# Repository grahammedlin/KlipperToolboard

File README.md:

# Huvud 3D Printer toolhead board USB-PD

A very small 3D printer board for use on a direct drive toolhead. 
It is designed to be used with Klipper firmware.
Klipper has the awesome feature to be able to use multiple MCUs connected to the host over a (relatively) high latency connection. 
This version uses USB-PD instead of CAN. 
Why? USB-C adoption makes premade, robust, and flexible cables capable of supplying power and data generally availabile as commodities.
Also, for fun.
It runs at 20 V instead of 24 V, so maximum fan speed is a little slower. 
24 V is technically possible with USB-PD 3.1 EPR AVS, but the hardware is not commonplace. 

---

Based on the amazing work of [bondus](https://github.com/bondus/KlipperToolboard)

Buy it at:

* Lukes Lab: https://lukeslabonline.com/products/huvud
* Tindie: https://www.tindie.com/products/huvud/huvud-3d-printer-hotend-control-board/

Read more about the project activites over at hackaday:
https://hackaday.io/project/174429-huvud-a-3d-printer-tool-head-controller-board

---

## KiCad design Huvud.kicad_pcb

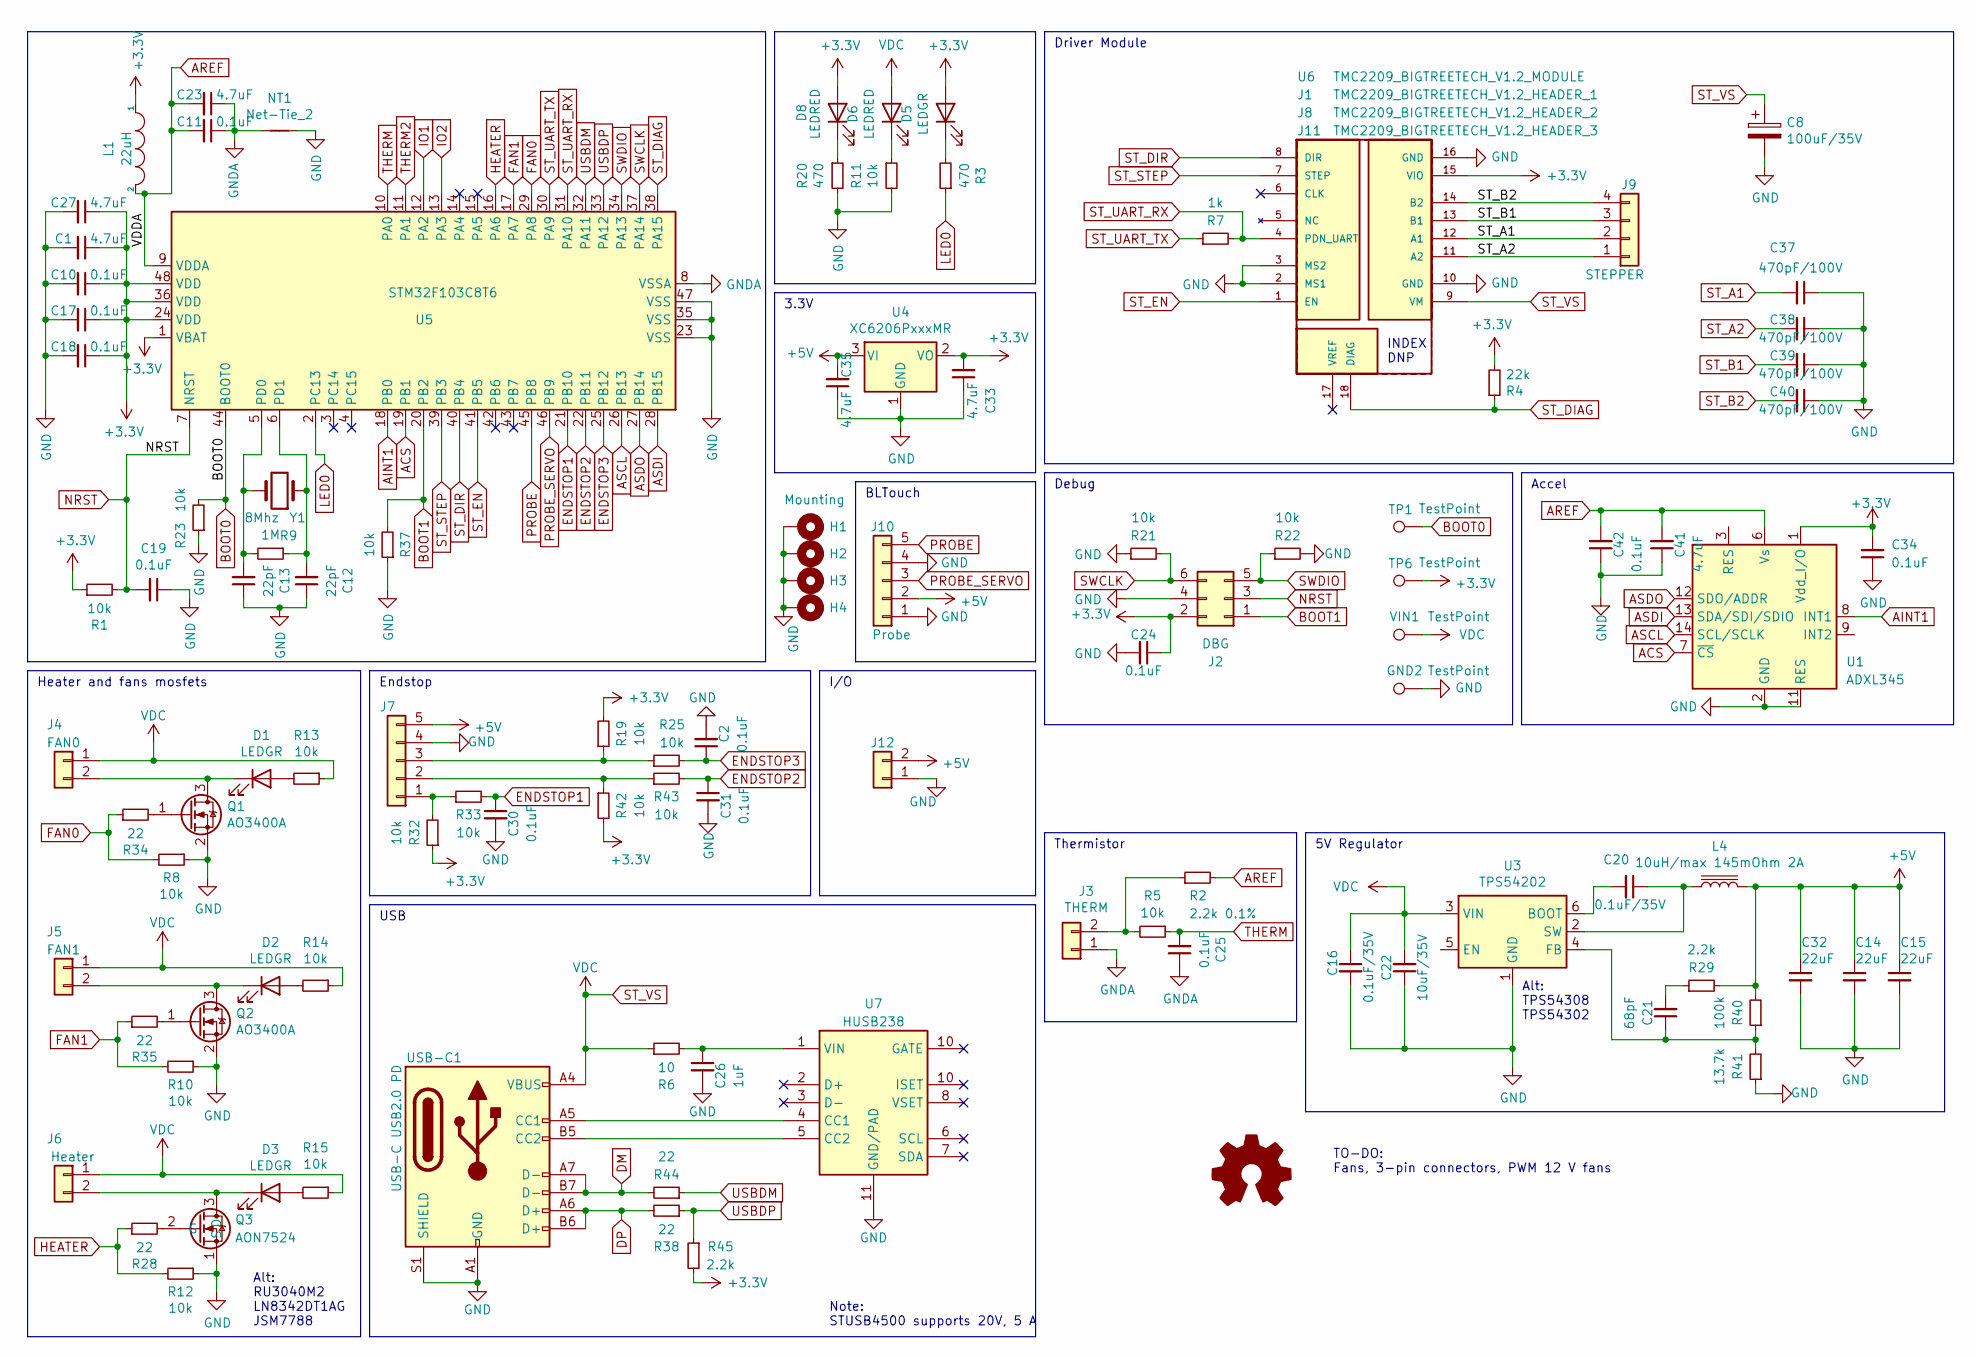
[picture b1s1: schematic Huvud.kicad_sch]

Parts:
C1, C23, C27, C33, C35, C41: 4.7uF; C_0402_1005Metric; LCSC C23733
C2, C11, C17, C18, C19, C24, C25, C30, C31: 0.1uF; C_0402_1005Metric
C8: 100uF/35V; CP_Elec_6.3x5.8; LCSC C249982
C10, C34, C42: 0.1uF; C_0402_1005Metric; LCSC C1525
C12: 22pF; C_0402_1005Metric; LCSC C1555
C13: 22pF; C_0402_1005Metric
C14, C15, C32: 22uF; C_0805_2012Metric; LCSC C45783
C16, C20: 0.1uF/35V; C_0603_1608Metric; LCSC C14663
C21: 68pF; C_0402_1005Metric; LCSC C14441
C22: 10uF/35V; C_1210_3225Metric; LCSC C13585
C26: 1uF; C_0402_1005Metric
C37, C38, C39, C40: 470pF/100V; C_0603_1608Metric; LCSC C107062
D1, D2, D3, D5: LEDGR; LED_0402_1005Metric; LCSC C74338
D6, D8: LEDRED; LED_0603_1608Metric; LCSC C2286
GND2: TestPoint; TestPoint_Pad_D1.0mm
H1: Mounting; MountingHole_3.2mm_M3_Pad_Via
H2, H3, H4: MountingHole; MountingHole_3.2mm_M3_Pad_Via
J1: TMC2209_BIGTREETECH_V1.2_HEADER_1; HEADER_TMC2209_BIGTREETECH_1
J2: DBG; PinHeader_2x03_P2.54mm_Vertical; LCSC C65114
J3: THERM; JST_PH_B2B-PH-K_1x02_P2.00mm_Vertical; LCSC C2320
J4: FAN0; JST_PH_B2B-PH-K_1x02_P2.00mm_Vertical; LCSC C2319
J5: FAN1; JST_PH_B2B-PH-K_1x02_P2.00mm_Vertical; LCSC C2319
J6: Heater; TerminalBlock_TE_282834-2_1x02_P2.54mm_Horizontal; LCSC C557685
J7: Endstop; JST_PH_B5B-PH-K_1x05_P2.00mm_Vertical; LCSC C2322
J8: TMC2209_BIGTREETECH_V1.2_HEADER_2; HEADER_TMC2209_BIGTREETECH_2
J9: STEPPER; JST_PH_B4B-PH-K_1x04_P2.00mm_Vertical; LCSC C144395
J10: Probe; PinHeader_1x05_P2.54mm_Vertical; LCSC C2322
J11: TMC2209_BIGTREETECH_V1.2_HEADER_3; HEADER_TMC2209_BIGTREETECH_3
J12: 5V; PinHeader_1x02_P2.54mm_Vertical; LCSC C2322
L1: 22uH; L_0805_2012Metric; LCSC C32375
L4: 10uH/max 145mOhm 2A; L_Sunlord_MWSA0518_5.4x5.2mm; LCSC C408412
LOGO1: Logo_Open_Hardware_Small; OSHW-Symbol_6.7x6mm_SilkScreen
NT1: Net-Tie_2; NetTie-2_SMD_Pad0.5mm
Q1, Q2: AO3400A; SOT-23; LCSC C20917
Q3: AON7524; DFN-8-1EP_3x3mm_P0.65mm_EP1.7x2.05mm; LCSC C431195
R1, R5, R8, R10, R12, R13, R14, R15, R21, R23: 10k; R_0402_1005Metric; LCSC C25744
R2: 2.2k 0.1%; R_0402_1005Metric; LCSC C445604
R3, R20: 470; R_0402_1005Metric; LCSC C25117
R4: 22k; R_0402_1005Metric; LCSC C25768
R6: 10; R_0402_1005Metric; LCSC C25744
R7: 1k; R_0402_1005Metric; LCSC C21190
R9: 1M; R_0402_1005Metric; LCSC C26083
R11, R19, R22, R25, R32, R33, R37, R42, R43: 10k; R_0402_1005Metric
R28, R35, R44: 22; R_0402_1005Metric
R29, R45: 2.2k; R_0402_1005Metric; LCSC C25879
R34, R38: 22; R_0402_1005Metric; LCSC C25092
R40: 100k; R_0402_1005Metric; LCSC C25741
R41: 13.7k; R_0402_1005Metric; LCSC C25854
TP1, TP6: TestPoint; TestPoint_Pad_D1.0mm
U1: ADXL345; LGA-14_3x5mm_P0.8mm_LayoutBorder1x6y; LCSC C9667
U3: TPS54202; SOT-23-6; LCSC C191884
U4: XC6206PxxxMR; SOT-23; LCSC C5446
U5: STM32F103C8T6; LQFP-48_7x7mm_P0.5mm; LCSC C8734
U6: TMC2209_BIGTREETECH_V1.2_MODULE; MODULE_TMC2209_BIGTREETECH; PARTREV 1.20
U7: HUSB238; DFN-10-1EP_3x3mm_P0.5mm_EP1.7x2.5mm
USB-C1: USB-C USB2.0 PD; USB_C_Receptacle_GT-USB-7010
VIN1: TestPoint; TestPoint_Pad_D1.0mm
Y1: 8Mhz; Crystal_SMD_5032-2Pin_5.0x3.2mm; LCSC C115962

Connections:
+3V3: C1.1, C10.1, C17.1, C18.1, C24.1, C27.1, C33.2, C34.2, D5.2 (A), D8.2 (A), J2.2, J8.15 (VIO), L1.1, R1.1, R4.2, R19.2, R32.1, R42.2, R45.2, TP6.1, U1.1 (Vdd_I/O), U4.2 (VO), U5.1 (VBAT), U5.24 (VDD), U5.36 (VDD), U5.48 (VDD)
+5V: C14.1, C15.1, C32.1, C35.2, J7.5, J10.2, J12.2, L4.2, R29.2, R40.2, U4.3 (VI)
ACS: U1.7 (~CS), U5.19 (PB1)
AINT1: U1.8 (INT1), U5.18 (PB0)
AREF: C11.2, C23.2, C41.2, C42.2, L1.2, R2.2, U1.6 (Vs), U5.9 (VDDA)
ASCL: U1.14 (SCL/SCLK), U5.26 (PB13)
ASDI: U1.13 (SDA/SDI/SDIO), U5.28 (PB15)
ASDO: U1.12 (SDO/ADDR), U5.27 (PB14)
BOOT0: R23.2, TP1.1, U5.44 (BOOT0)
BOOT1: J2.1, R37.2, U5.20 (PB2)
DM: R44.2, USB-C1.A7 (D-), USB-C1.B7 (D-)
DP: R38.2, USB-C1.A6 (D+), USB-C1.B6 (D+)
ENDSTOP1: C30.1, R33.2, U5.21 (PB10)
ENDSTOP2: C31.1, R43.2, U5.22 (PB11)
ENDSTOP3: C2.1, R25.2, U5.25 (PB12)
FAN0: R8.2, R34.1, U5.29 (PA8)
FAN1: R10.2, R35.1, U5.17 (PA7)
GND: C1.2, C2.2, C8.2, C10.2, C12.1, C13.1, C14.2, C15.2, C16.2, C17.2, C18.2, C19.1, C22.1, C24.2, C26.2, C27.2, C30.2, C31.2, C32.2, C33.1, C34.1, C35.1, C37.1, C38.1, C39.1, C40.1, C41.1, C42.1, GND2.1, H1.1, H2.1, H3.1, H4.1, J1.2 (MS1), J1.3 (MS2), J2.4, J7.4, J8.10 (GND), J8.16 (GND), J10.1, J10.4, J12.1, NT1.1, Q1.2 (S), Q2.2 (S), Q3.1 (S), R8.1, R10.1, R11.2, R12.1, R20.2, R21.1, R22.2, R23.1, R37.1, R41.1, U1.2 (GND), U1.4 (GND), U1.5 (GND), U1.11 (RES), U3.1 (GND), U4.1 (GND), U5.23 (VSS), U5.35 (VSS), U5.47 (VSS), U7.11 (GND/PAD), USB-C1.A1 (GND), USB-C1.A12 (GND), USB-C1.B1 (GND), USB-C1.B12 (GND), USB-C1.S1 (SHIELD)
GNDA: C11.1, C23.1, C25.1, J3.1, NT1.2, U5.8 (VSSA)
HEATER: R12.2, R28.1, U5.16 (PA6)
IO1: U5.12 (PA2)
IO2: U5.13 (PA3)
LED0: R3.1, U5.2 (PC13)
NRST: C19.2, J2.3, R1.2, U5.7 (NRST)
unnamed: C21.2, R29.1
unnamed: D1.2 (A), R13.2
unnamed: D1.1 (K), J4.2, Q1.3 (D)
unnamed: D2.2 (A), R14.2
unnamed: D2.1 (K), J5.2, Q2.3 (D)
unnamed: D3.2 (A), R15.2
unnamed: D3.1 (K), J6.2, Q3.3 (D)
unnamed: D5.1 (K), R3.2
unnamed: D6.1 (K), R11.1
unnamed: D8.1 (K), R20.1
unnamed: J3.2, R2.1, R5.2
unnamed: J7.1, R32.2, R33.1
unnamed: J7.2, R42.1, R43.1
unnamed: J7.3, R19.1, R25.1
unnamed: Q1.1 (G), R34.2
unnamed: Q2.1 (G), R35.2
unnamed: Q3.2 (G), R28.2
unnamed: C20.2, U3.6 (BOOT)
unnamed: C21.1, R40.1, R41.2, U3.4 (FB)
unnamed: C20.1, L4.1, U3.2 (SW)
unnamed: C13.2, R9.2, U5.5 (PD0), Y1.2
unnamed: C12.2, R9.1, U5.6 (PD1), Y1.1
unnamed: U7.4 (CC1), USB-C1.A5 (CC1)
unnamed: U7.5 (CC2), USB-C1.B5 (CC2)
unnamed: C26.1, R6.2, U7.1 (VIN)
PROBE: J10.5, U5.45 (PB8)
PROBE_SERVO: J10.3, U5.46 (PB9)
ST_A1: C37.2, J8.12 (A1), J9.2
ST_A2: C38.2, J8.11 (A2), J9.1
ST_B1: C39.2, J8.13 (B1), J9.3
ST_B2: C40.2, J8.14 (B2), J9.4
ST_DIAG: J11.18 (DIAG), R4.1, U5.38 (PA15)
ST_DIR: J1.8 (DIR), U5.40 (PB4)
ST_EN: J1.1 (EN), U5.41 (PB5)
ST_STEP: J1.7 (STEP), U5.39 (PB3)
ST_UART_RX: J1.4 (PDN_UART), R7.2, U5.31 (PA10)
ST_UART_TX: R7.1, U5.30 (PA9)
ST_VS: C8.1, C16.1, C22.2, D6.2 (A), J4.1, J5.1, J6.1, J8.9 (VM), R6.1, R13.1, R14.1, R15.1, U3.3 (VIN), USB-C1.A4 (VBUS), USB-C1.A9 (VBUS), USB-C1.B4 (VBUS), USB-C1.B9 (VBUS), VIN1.1
SWCLK: J2.6, R21.2, U5.37 (PA14)
SWDIO: J2.5, R22.1, U5.34 (PA13)
THERM: C25.2, R5.1, U5.10 (PA0)
THERM2: U5.11 (PA1)
USBDM: R44.1, U5.32 (PA11)
USBDP: R38.1, R45.1, U5.33 (PA12)

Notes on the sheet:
3.3V
5V Regulator
Endstop
I/O
Debug
Note: STUSB4500 supports 20V, 5 A
Driver Module
TO-DO: Fans, 3-pin connectors, PWM 12 V fans
Alt: RU3040M2 LN8342DT1AG JSM7788
Thermistor
Heater and fans mosfets
USB
Accel
Alt: TPS54308 TPS54302
BLTouch
INDEX DNP

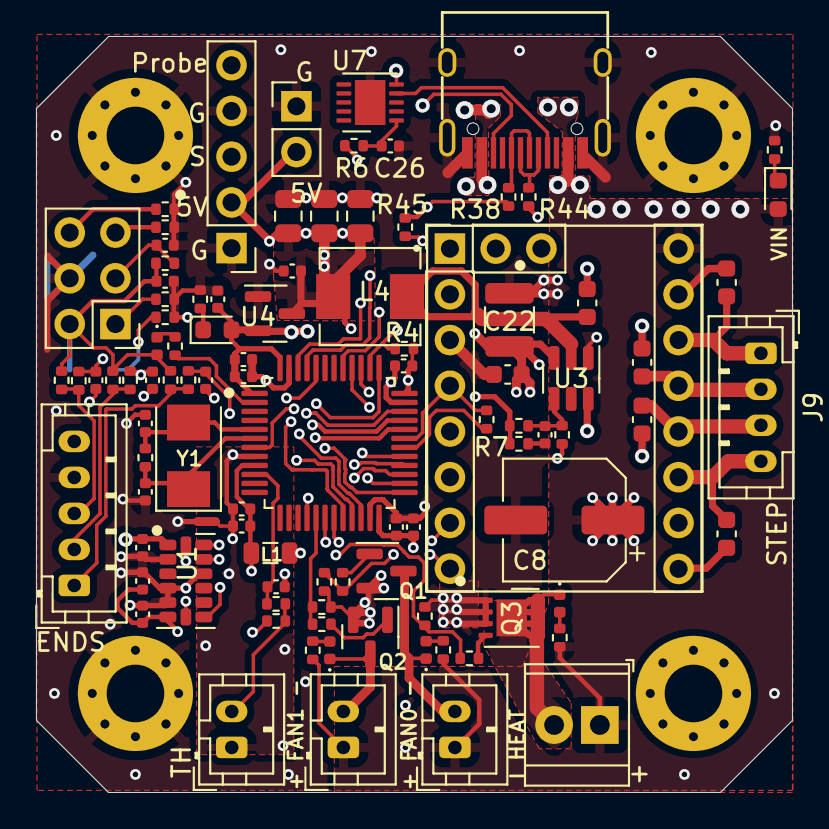
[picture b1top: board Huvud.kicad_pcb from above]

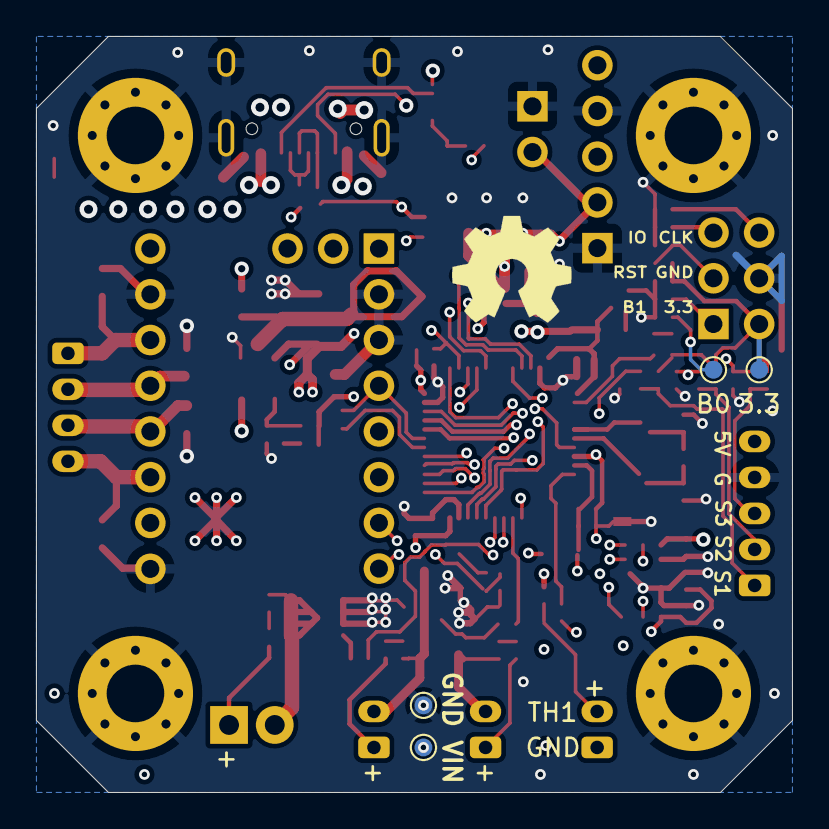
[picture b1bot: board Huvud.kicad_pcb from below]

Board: 4 copper layers, 42.0 x 42.0 mm, 109 parts (5 on the bottom side), 65 nets.

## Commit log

2023-02-28 replace CAN with USB-C PD, remove other version
2023-03-03 repace TMC2209 with module
2023-03-04 re-layout
2023-03-04 cleanup and bom
